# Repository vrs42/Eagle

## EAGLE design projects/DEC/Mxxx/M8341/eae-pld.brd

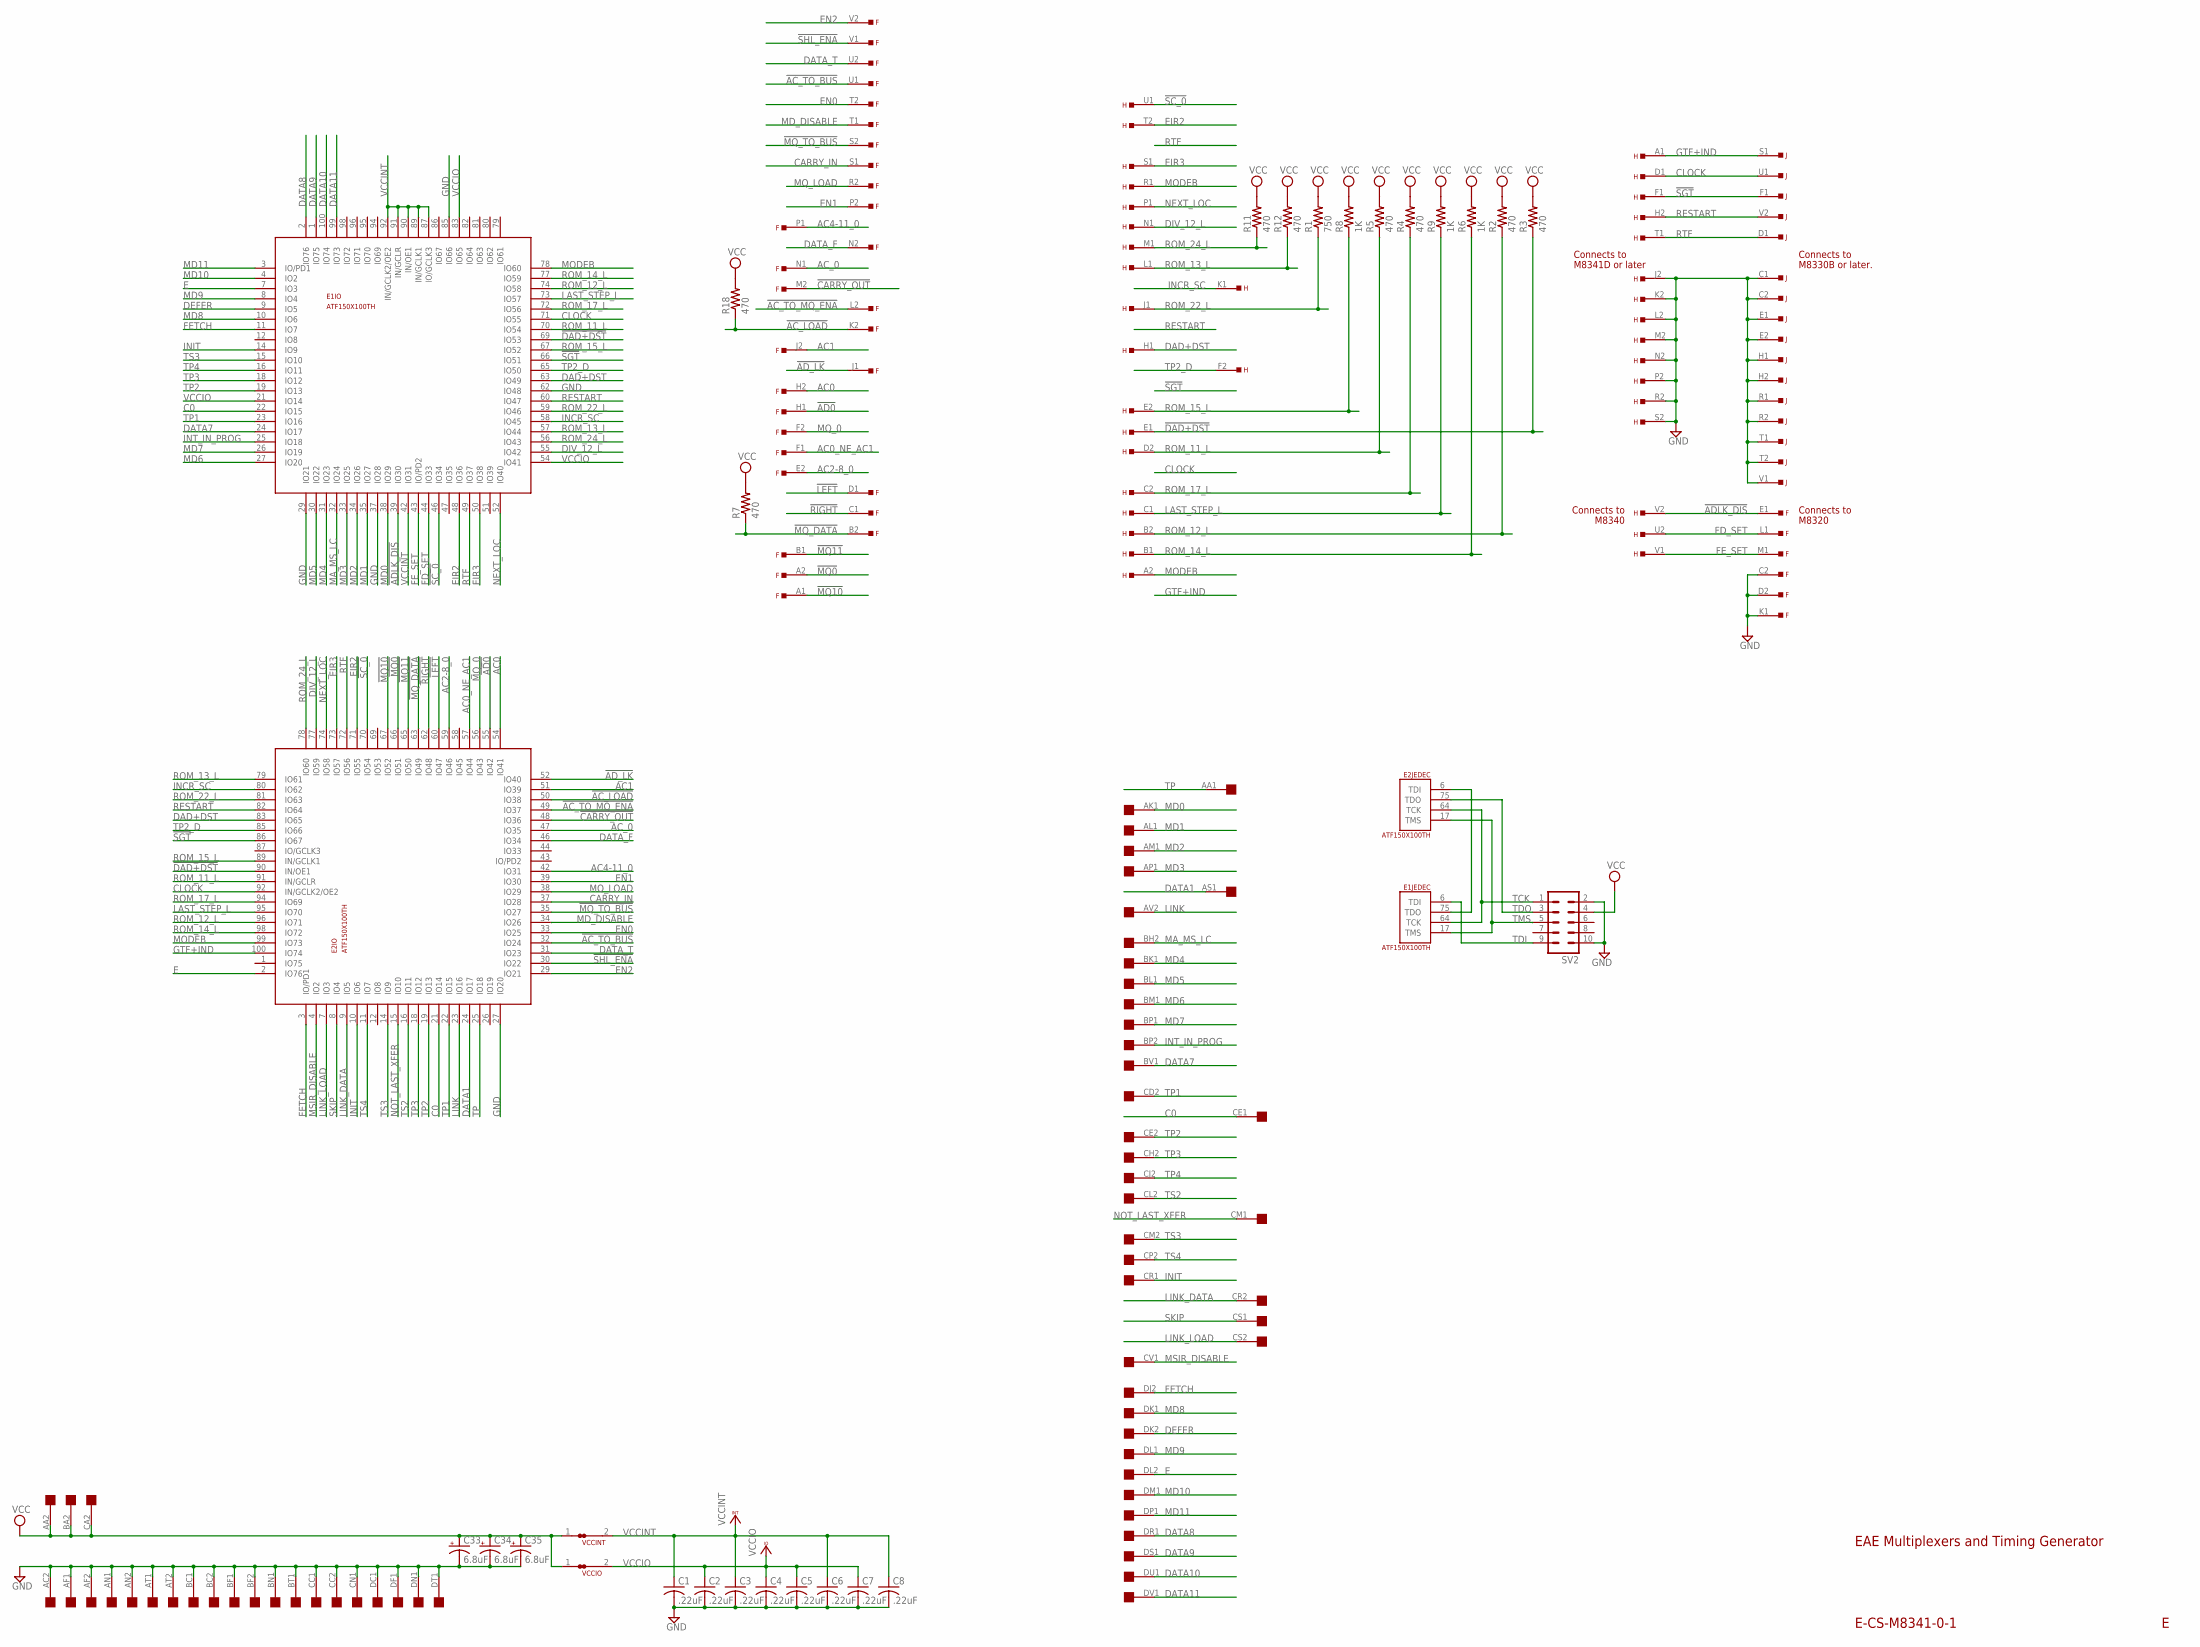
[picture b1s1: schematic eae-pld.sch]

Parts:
C1, C2, C3, C4, C5, C6, C7, C8: .22uF; C063-025X075
C33, C34, C35: 6.8uF; E12-8
E1, E2: ATF150X100TH; TH-100
F: EDGE-TOP; EDGE-CON2
H: EDGE-TOP; EDGE-CON2
J: EDGE-TOP; EDGE-CON2
R1: 750; 0207/10
R2, R3, R4, R5, R7, R11, R12, R18: 470; 0207/10
R6, R8, R9: 1K; 0207/10
SV2: ML10
U$1: QUAD; EDGE-CON8
VCCINT: JUMPER-NC1; NC1
VCCIO: JUMPER-NC1; NC1

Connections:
!AC_LOAD: E2.50 (IO38), F.K2, R18.1
!AC_TO_BUS: E2.32 (IO24), F.U1
!AC_TO_MQ_ENA: E2.49 (IO37), F.L2
!AD0: E2.55 (IO42), F.H1
!ADLK_DIS: E1.39 (IO30), F.E1, H.V2
!AD_LK: E2.52 (IO40), F.J1
!CARRY_OUT: E2.48 (IO36), F.M2
!DAD+DST: E1.69 (IO53), E2.90 (IN/OE1), H.E1, R3.1
!LEFT: E2.60 (IO47), F.D1
!MQ0: E2.66 (IO51), F.A2
!MQ10: E2.67 (IO52), F.A1
!MQ11: E2.65 (IO50), F.B1
!MQ_DATA: E2.63 (IO49), F.B2, R7.1
!MQ_TO_BUS: E2.35 (IO27), F.S2
!RIGHT: E2.62 (IO48), F.C1
!SC_0: E1.46 (IO34), E2.70 (IO54), H.U1
!SGT: E1.66 (IO51), E2.86 (IO67), H.F1, J.F1
!SHL_ENA: E2.30 (IO22), F.V1
AC0: E2.54 (IO41), F.H2
AC0_NE_AC1: E2.57 (IO44), F.F1
AC1: E2.51 (IO39), F.J2
AC2-8_0: E2.59 (IO46), F.E2
AC4-11_0: E2.42 (IO31), F.P1
AC_0: E2.47 (IO35), F.N1
C0: E1.22 (IO15), E2.21 (IO14), U$1.CE1
CARRY_IN: E2.37 (IO28), F.S1
CLOCK: E1.71 (IO55), E2.92 (IN/GCLK2/OE2), H.D1, J.U1
DAD+DST: E1.63 (IO49), E2.83 (IO65), H.H1
DATA1: E2.24 (IO17), U$1.AS1
DATA7: E1.24 (IO17), U$1.BV1
DATA8: E1.2 (IO76), U$1.DR1
DATA9: E1.1 (IO75), U$1.DS1
DATA10: E1.100 (IO74), U$1.DU1
DATA11: E1.99 (IO73), U$1.DV1
DATA_F: E2.46 (IO34), F.N2
DATA_T: E2.31 (IO23), F.U2
DEFER: E1.9 (IO5), U$1.DK2
DIV_12_L: E1.55 (IO42), E2.77 (IO59), H.N1
E: E1.7 (IO3), E2.2 (IO76), U$1.DL2
EIR2: E1.48 (IO36), E2.71 (IO55), H.T2
EIR3: E1.50 (IO38), E2.73 (IO57), H.S1
EN0: E2.33 (IO25), F.T2
EN1: E2.39 (IO30), F.P2
EN2: E2.29 (IO21), F.V2
FD_SET: E1.44 (IO33), F.L1, H.U2
FETCH: E1.11 (IO7), E2.3 (IO/PD1), U$1.DJ2
FE_SET: E1.43 (IO/PD2), F.M1, H.V1
GND: C1.2, C2.2, C3.2, C4.2, C5.2, C6.2, C7.2, C8.2, C33.-, C34.-, C35.-, E1.13 (GND), E1.28 (GND), E1.29 (IO21), E1.37 (IO28), E1.40 (GND), E1.45 (GND), E1.61 (GND), E1.62 (IO48), E1.76 (GND), E1.85 (IO66), E1.88 (GND), E1.97 (GND), E2.13 (GND), E2.27 (IO20), E2.28 (GND), E2.40 (GND), E2.45 (GND), E2.61 (GND), E2.76 (GND), E2.88 (GND), E2.97 (GND), F.C2, F.D2, F.K1, H.J2, H.K2, H.L2, H.M2, H.N2, H.P2, H.R2, H.S2, J.C1, J.C2, J.E1, J.E2, J.H1, J.H2, J.R1, J.R2, J.T1, J.T2, J.V1, SV2.2, SV2.10, U$1.AC2, U$1.AF1, U$1.AF2, U$1.AN1, U$1.AN2, U$1.AT1, U$1.AT2, U$1.BC1, U$1.BC2, U$1.BF1, U$1.BF2, U$1.BN1, U$1.BT1, U$1.CC1, U$1.CC2, U$1.CN1, U$1.DC1, U$1.DF1, U$1.DN1, U$1.DT1
GTF+IND: E2.100 (IO74), H.A1, J.S1
INCR_SC: E1.58 (IO45), E2.80 (IO62), H.K1
INIT: E1.14 (IO9), E2.10 (IO6), U$1.CR1
INT_IN_PROG: E1.25 (IO18), U$1.BP2
LAST_STEP_L: E1.73 (IO57), E2.95 (IO70), H.C1, R9.1
LINK: E2.23 (IO16), U$1.AV2
LINK_DATA: E2.9 (IO5), U$1.CR2
LINK_LOAD: E2.7 (IO3), U$1.CS2
MA_MS_LC: E1.32 (IO24), U$1.BH2
MD0: E1.38 (IO29), U$1.AK1
MD1: E1.35 (IO27), U$1.AL1
MD2: E1.34 (IO26), U$1.AM1
MD3: E1.33 (IO25), U$1.AP1
MD4: E1.31 (IO23), U$1.BK1
MD5: E1.30 (IO22), U$1.BL1
MD6: E1.27 (IO20), U$1.BM1
MD7: E1.26 (IO19), U$1.BP1
MD8: E1.10 (IO6), U$1.DK1
MD9: E1.8 (IO4), U$1.DL1
MD10: E1.4 (IO2), U$1.DM1
MD11: E1.3 (IO/PD1), U$1.DP1
MD_DISABLE: E2.34 (IO26), F.T1
MODEB: E1.78 (IO60), E2.99 (IO73), H.A2, H.R1
MQ_0: E2.56 (IO43), F.F2
MQ_LOAD: E2.38 (IO29), F.R2
MSIR_DISABLE: E2.4 (IO2), U$1.CV1
NEXT_LOC: E1.52 (IO40), E2.74 (IO58), H.P1
NOT_LAST_XFER: E2.15 (IO10), U$1.CM1
RESTART: E1.60 (IO47), E2.82 (IO64), H.H2, J.V2
ROM_11_L: E1.70 (IO54), E2.91 (IN/GCLR), H.D2, R5.1
ROM_12_L: E1.74 (IO58), E2.96 (IO71), H.B2, R2.1
ROM_13_L: E1.57 (IO44), E2.79 (IO61), H.L1, R12.1
ROM_14_L: E1.77 (IO59), E2.98 (IO72), H.B1, R6.1
ROM_15_L: E1.67 (IO52), E2.89 (IN/GCLK1), H.E2, R8.1
ROM_17_L: E1.72 (IO56), E2.94 (IO69), H.C2, R4.1
ROM_22_L: E1.59 (IO46), E2.81 (IO63), H.J1, R1.1
ROM_24_L: E1.56 (IO43), E2.78 (IO60), H.M1, R11.1
RTF: E1.49 (IO37), E2.72 (IO56), H.T1, J.D1
SKIP: E2.8 (IO4), U$1.CS1
TCK: E1.64 (TCK), E2.64 (TCK), SV2.1
TDI: E1.6 (TDI), SV2.9
TDIO: E1.75 (TDO), E2.6 (TDI)
TDO: E2.75 (TDO), SV2.3
TMS: E1.17 (TMS), E2.17 (TMS), SV2.5
TP: E2.25 (IO18), U$1.AA1
TP1: E1.23 (IO16), E2.22 (IO15), U$1.CD2
TP2: E1.19 (IO13), E2.19 (IO13), U$1.CE2
TP2_D: E1.65 (IO50), E2.85 (IO66), H.F2
TP3: E1.18 (IO12), E2.18 (IO12), U$1.CH2
TP4: E1.16 (IO11), U$1.CJ2
TS2: E2.16 (IO11), U$1.CL2
TS3: E1.15 (IO10), E2.14 (IO9), U$1.CM2
TS4: E2.11 (IO7), U$1.CP2
VCC: C33.+, C34.+, C35.+, R1.2, R2.2, R3.2, R4.2, R5.2, R6.2, R7.2, R8.2, R9.2, R11.2, R12.2, R18.2, SV2.4, U$1.AA2, U$1.BA2, U$1.CA2, VCCINT.1, VCCIO.1
VCCINT: C1.1, C3.1, C6.1, C8.1, E1.41 (VCCINT), E1.42 (IO31), E1.87 (IO/GCLK3), E1.89 (IN/GCLK1), E1.90 (IN/OE1), E1.91 (IN/GCLR), E1.92 (IN/GCLK2/OE2), E1.93 (VCCINT), E2.41 (VCCINT), E2.93 (VCCINT), VCCINT.2
VCCIO: C2.1, C4.1, C5.1, C7.1, E1.5 (VCCIO), E1.20 (VCCIO), E1.21 (IO14), E1.36 (VCCIO), E1.53 (VCCIO), E1.54 (IO41), E1.68 (VCCIO), E1.83 (IO65), E1.84 (VCCIO), E2.5 (VCCIO), E2.20 (VCCIO), E2.36 (VCCIO), E2.53 (VCCIO), E2.68 (VCCIO), E2.84 (VCCIO), VCCIO.2

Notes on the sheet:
E-CS-M8341-0-1
EAE Multiplexers and Timing Generator
M8320
Connects to
M8340
M8330B or later.
M8341D or later

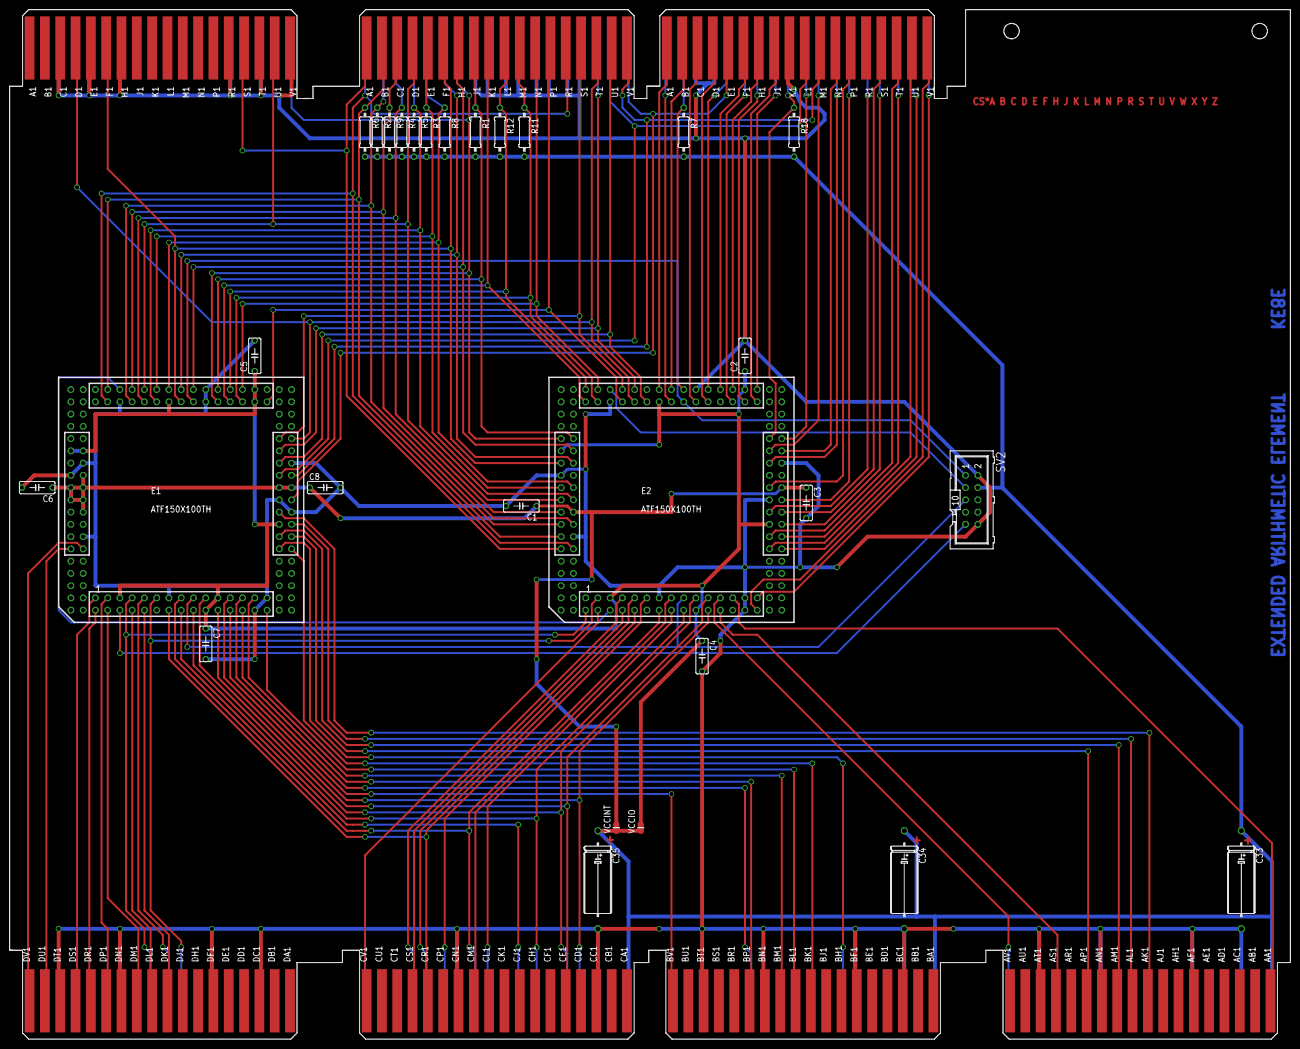
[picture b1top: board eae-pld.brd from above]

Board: 2 copper layers, 265.4 x 213.4 mm, 32 parts (0 on the bottom side), 104 nets.

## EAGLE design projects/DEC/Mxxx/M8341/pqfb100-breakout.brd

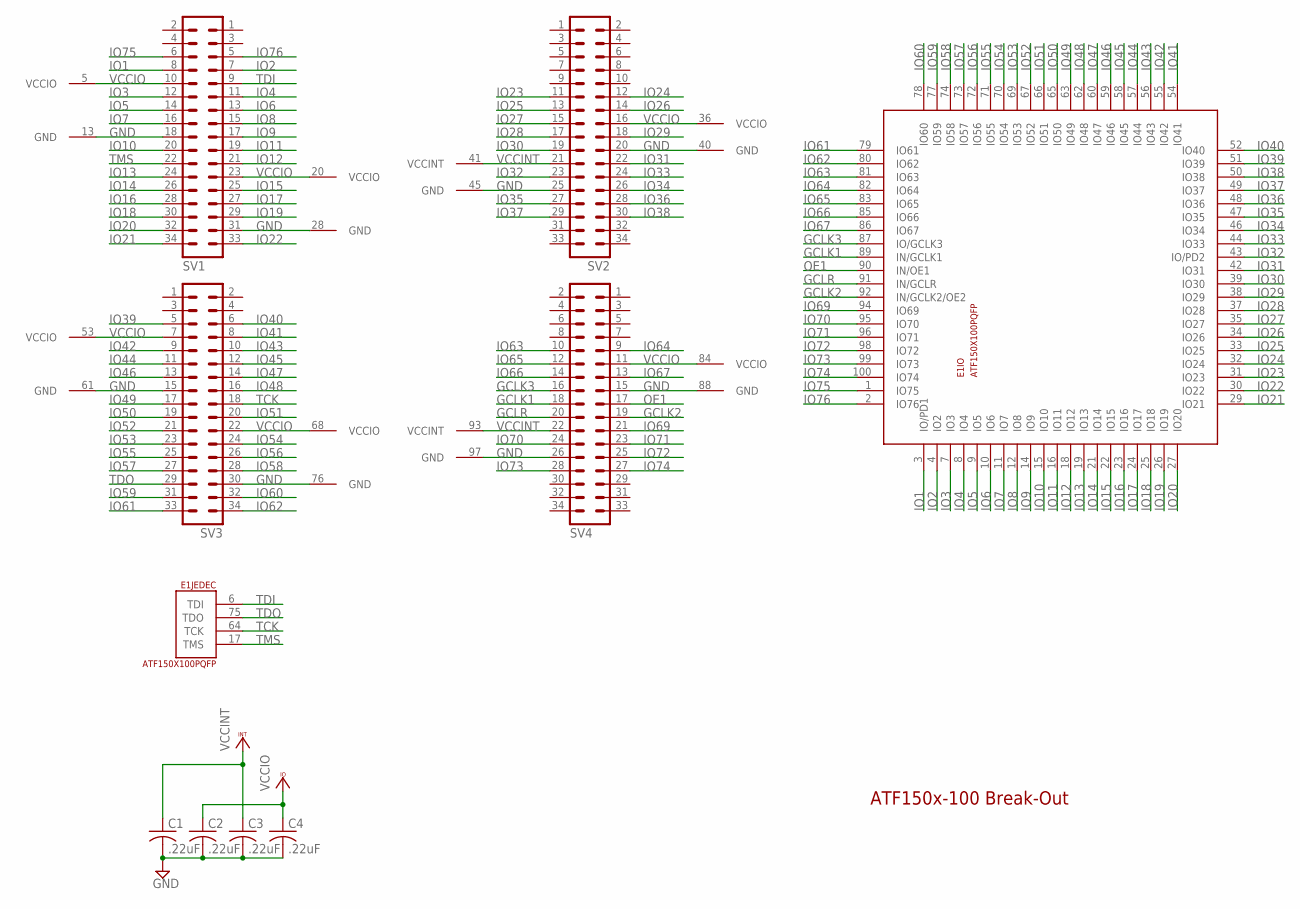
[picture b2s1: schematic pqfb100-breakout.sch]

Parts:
C1, C2, C3, C4: .22uF; C063-025X075
E1: ATF150X100PQFP; PQFP-100
SV1, SV2, SV3, SV4: MA17-2

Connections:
GCLK1: E1.89 (IN/GCLK1), SV4.18
GCLK2: E1.92 (IN/GCLK2/OE2), SV4.19
GCLK3: E1.87 (IO/GCLK3), SV4.16
GCLR: E1.91 (IN/GCLR), SV4.20
GND: C1.2, C2.2, C3.2, C4.2, E1.13 (GND), E1.28 (GND), E1.40 (GND), E1.45 (GND), E1.61 (GND), E1.76 (GND), E1.88 (GND), E1.97 (GND), SV1.18, SV1.31, SV2.20, SV2.25, SV3.15, SV3.30, SV4.15, SV4.26
IO1: E1.3 (IO/PD1), SV1.8
IO2: E1.4 (IO2), SV1.7
IO3: E1.7 (IO3), SV1.12
IO4: E1.8 (IO4), SV1.11
IO5: E1.9 (IO5), SV1.14
IO6: E1.10 (IO6), SV1.13
IO7: E1.11 (IO7), SV1.16
IO8: E1.12 (IO8), SV1.15
IO9: E1.14 (IO9), SV1.17
IO10: E1.15 (IO10), SV1.20
IO11: E1.16 (IO11), SV1.19
IO12: E1.18 (IO12), SV1.21
IO13: E1.19 (IO13), SV1.24
IO14: E1.21 (IO14), SV1.26
IO15: E1.22 (IO15), SV1.25
IO16: E1.23 (IO16), SV1.28
IO17: E1.24 (IO17), SV1.27
IO18: E1.25 (IO18), SV1.30
IO19: E1.26 (IO19), SV1.29
IO20: E1.27 (IO20), SV1.32
IO21: E1.29 (IO21), SV1.34
IO22: E1.30 (IO22), SV1.33
IO23: E1.31 (IO23), SV2.11
IO24: E1.32 (IO24), SV2.12
IO25: E1.33 (IO25), SV2.13
IO26: E1.34 (IO26), SV2.14
IO27: E1.35 (IO27), SV2.15
IO28: E1.37 (IO28), SV2.17
IO29: E1.38 (IO29), SV2.18
IO30: E1.39 (IO30), SV2.19
IO31: E1.42 (IO31), SV2.22
IO32: E1.43 (IO/PD2), SV2.23
IO33: E1.44 (IO33), SV2.24
IO34: E1.46 (IO34), SV2.26
IO35: E1.47 (IO35), SV2.27
IO36: E1.48 (IO36), SV2.28
IO37: E1.49 (IO37), SV2.29
IO38: E1.50 (IO38), SV2.30
IO39: E1.51 (IO39), SV3.5
IO40: E1.52 (IO40), SV3.6
IO41: E1.54 (IO41), SV3.8
IO42: E1.55 (IO42), SV3.9
IO43: E1.56 (IO43), SV3.10
IO44: E1.57 (IO44), SV3.11
IO45: E1.58 (IO45), SV3.12
IO46: E1.59 (IO46), SV3.13
IO47: E1.60 (IO47), SV3.14
IO48: E1.62 (IO48), SV3.16
IO49: E1.63 (IO49), SV3.17
IO50: E1.65 (IO50), SV3.19
IO51: E1.66 (IO51), SV3.20
IO52: E1.67 (IO52), SV3.21
IO53: E1.69 (IO53), SV3.23
IO54: E1.70 (IO54), SV3.24
IO55: E1.71 (IO55), SV3.25
IO56: E1.72 (IO56), SV3.26
IO57: E1.73 (IO57), SV3.27
IO58: E1.74 (IO58), SV3.28
IO59: E1.77 (IO59), SV3.31
IO60: E1.78 (IO60), SV3.32
IO61: E1.79 (IO61), SV3.33
IO62: E1.80 (IO62), SV3.34
IO63: E1.81 (IO63), SV4.10
IO64: E1.82 (IO64), SV4.9
IO65: E1.83 (IO65), SV4.12
IO66: E1.85 (IO66), SV4.14
IO67: E1.86 (IO67), SV4.13
IO69: E1.94 (IO69), SV4.21
IO70: E1.95 (IO70), SV4.24
IO71: E1.96 (IO71), SV4.23
IO72: E1.98 (IO72), SV4.25
IO73: E1.99 (IO73), SV4.28
IO74: E1.100 (IO74), SV4.27
IO75: E1.1 (IO75), SV1.6
IO76: E1.2 (IO76), SV1.5
OE1: E1.90 (IN/OE1), SV4.17
TCK: E1.64 (TCK), SV3.18
TDI: E1.6 (TDI), SV1.9
TDO: E1.75 (TDO), SV3.29
TMS: E1.17 (TMS), SV1.22
VCCINT: C1.1, C3.1, E1.41 (VCCINT), E1.93 (VCCINT), SV2.21, SV4.22
VCCIO: C2.1, C4.1, E1.5 (VCCIO), E1.20 (VCCIO), E1.36 (VCCIO), E1.53 (VCCIO), E1.68 (VCCIO), E1.84 (VCCIO), SV1.10, SV1.23, SV2.16, SV3.7, SV3.22, SV4.11

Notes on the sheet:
ATF150x-100 Break-Out

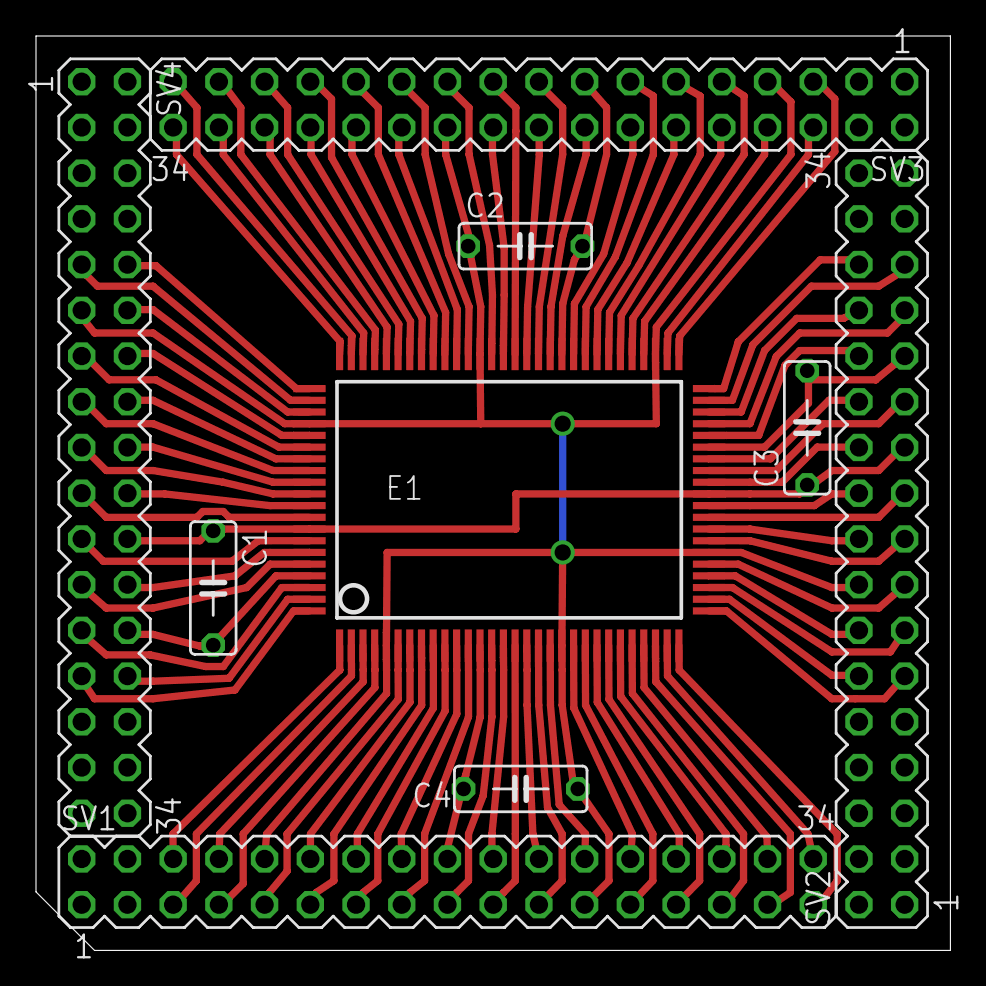
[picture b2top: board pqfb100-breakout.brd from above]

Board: 2 copper layers, 50.8 x 50.8 mm, 9 parts (0 on the bottom side), 87 nets.
